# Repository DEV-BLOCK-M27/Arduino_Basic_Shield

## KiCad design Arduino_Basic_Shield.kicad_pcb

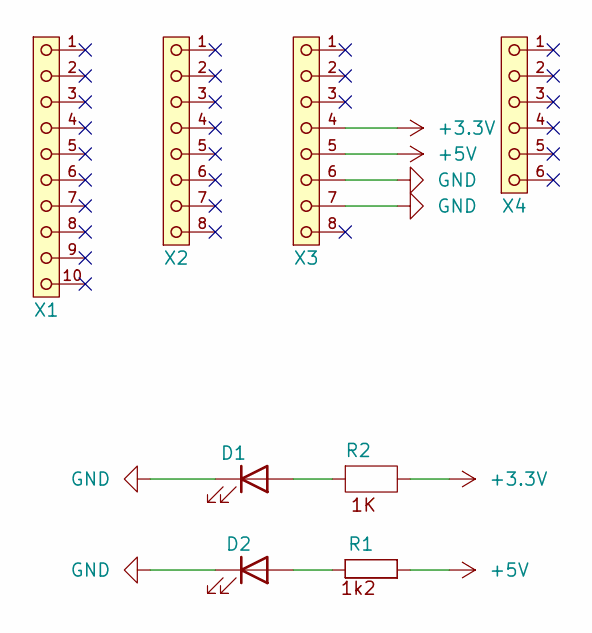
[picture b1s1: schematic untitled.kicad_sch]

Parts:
D1, D2: LED_0805; Manufacturer Part Number 150080RS75000; JLC C84256
R1: RES_0805; Manufacturer Part Number YAGEO; JLC C17379
R2: RES_0805; Manufacturer Part Number Vishay / Dale; JLC C17513
X1: CON_61301011121; Manufacturer Part Number 61301011121
X2, X3: CON_61300811121; Manufacturer Part Number 61300811121
X4: CON_61300611121; Manufacturer Part Number 61300611121

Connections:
+3.3V: R2.2, X3.4
+5V: R1.2, X3.5
GND: D1.K, D2.K, X3.6, X3.7
unnamed: D1.A, R2.1
unnamed: D2.A, R1.1

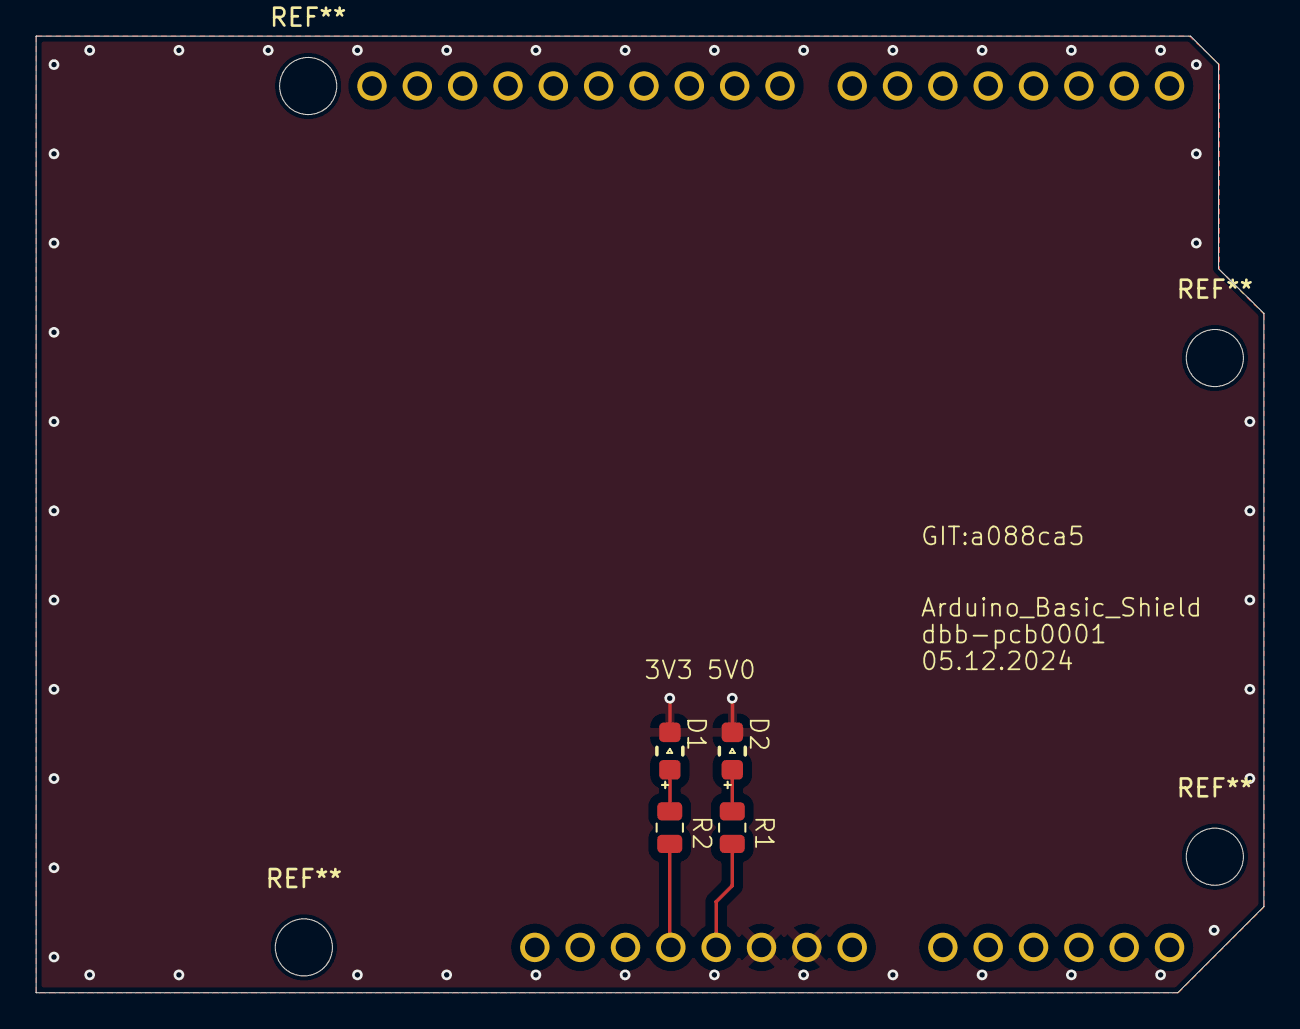
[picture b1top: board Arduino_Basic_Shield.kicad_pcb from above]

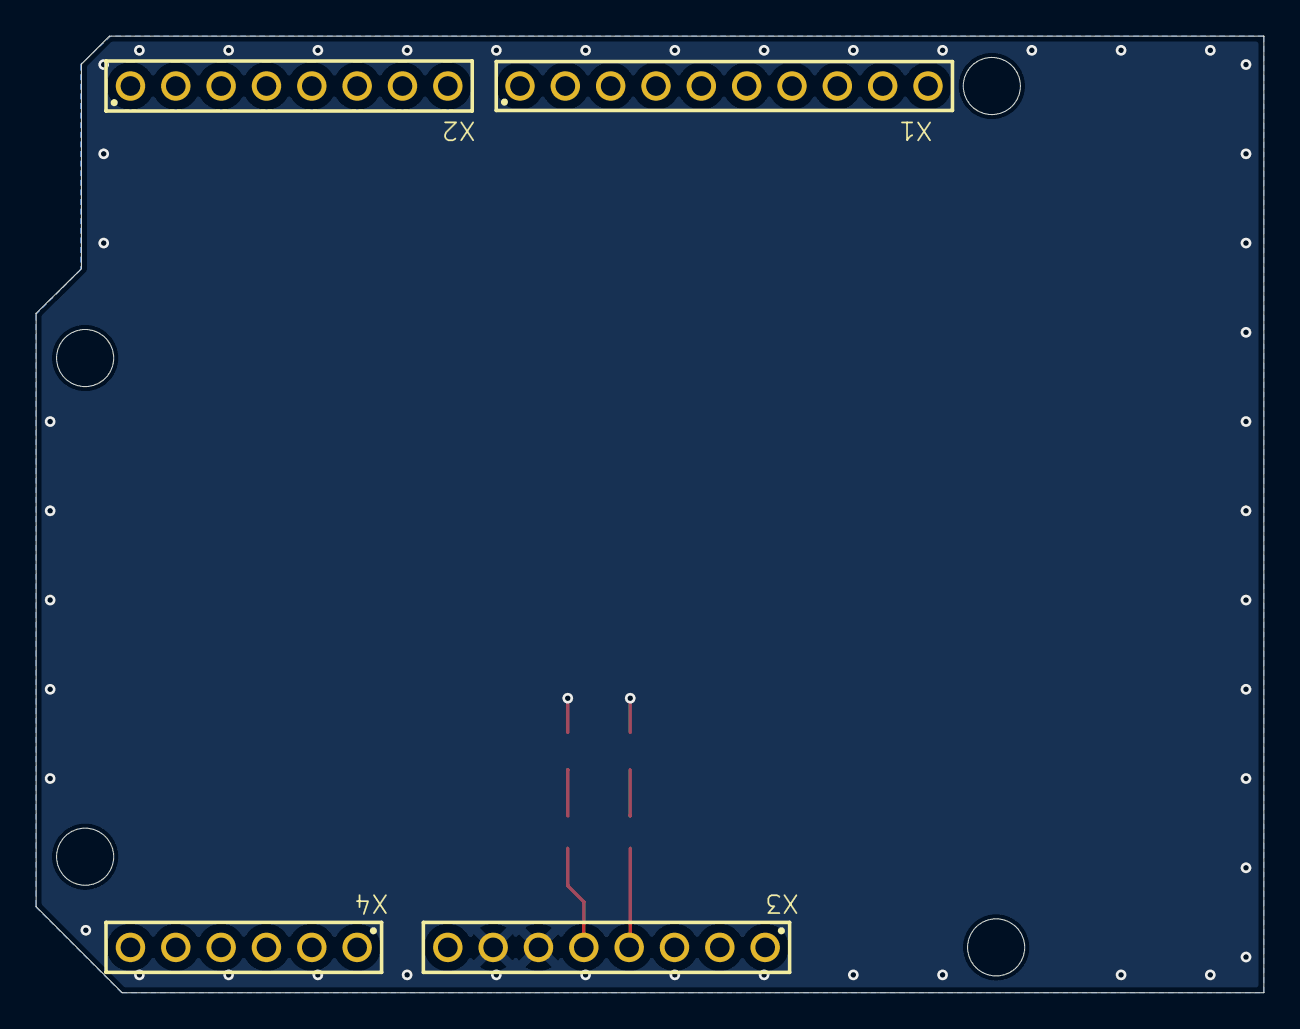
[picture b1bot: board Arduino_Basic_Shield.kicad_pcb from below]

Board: 2 copper layers, 68.8 x 53.6 mm, 8 parts (4 on the bottom side), 5 nets.

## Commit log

2024-12-05 Initial commit
    Add Basic Project Files
2024-12-06 add autodoc elemente
2024-12-08 update pcb
    add layer description
